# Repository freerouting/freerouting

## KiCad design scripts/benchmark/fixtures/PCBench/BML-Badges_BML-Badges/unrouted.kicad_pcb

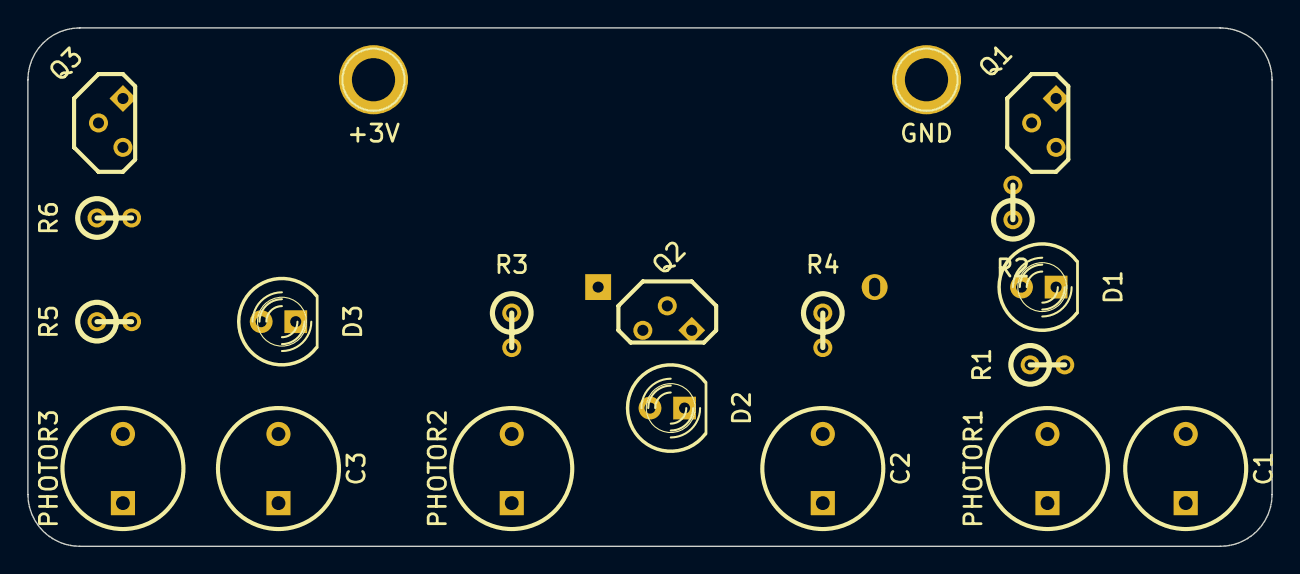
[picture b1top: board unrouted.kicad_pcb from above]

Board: 2 copper layers, 91.4 x 38.1 mm, 21 parts (1 on the bottom side), 11 nets, no tracks yet.

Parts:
BT1: 3V; BS-7-CR2032-2
C1, C2, C3: 22uF; C2V8
D1, D2, D3: LED; LED-5MM
P1: +3V; 1pin
P2: GND; 1pin
PHOTOR1, PHOTOR2, PHOTOR3: PHOTOR; LDR
Q1, Q2, Q3: PN2222A; TO92-EBC-num
R1, R3, R5: 330; R1
R2, R4, R6: 100k; R1

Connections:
3V: BT1.1, P1.1, R1.1, R2.1, R3.1, R4.1, R5.1, R6.1
GND: BT1.2, C1.2, C2.2, C3.2, P2.1, PHOTOR1.2, PHOTOR2.2, PHOTOR3.2, Q1.1, Q2.1, Q3.1
unnamed: C1.1, PHOTOR1.1, Q1.2, R2.2
unnamed: C2.1, PHOTOR2.1, Q2.2, R4.2
unnamed: C3.1, PHOTOR3.1, Q3.2, R6.2
unnamed: D1.1, R1.2
unnamed: D1.2, Q1.3
unnamed: D2.1, R3.2
unnamed: D2.2, Q2.3
unnamed: D3.1, R5.2
unnamed: D3.2, Q3.3

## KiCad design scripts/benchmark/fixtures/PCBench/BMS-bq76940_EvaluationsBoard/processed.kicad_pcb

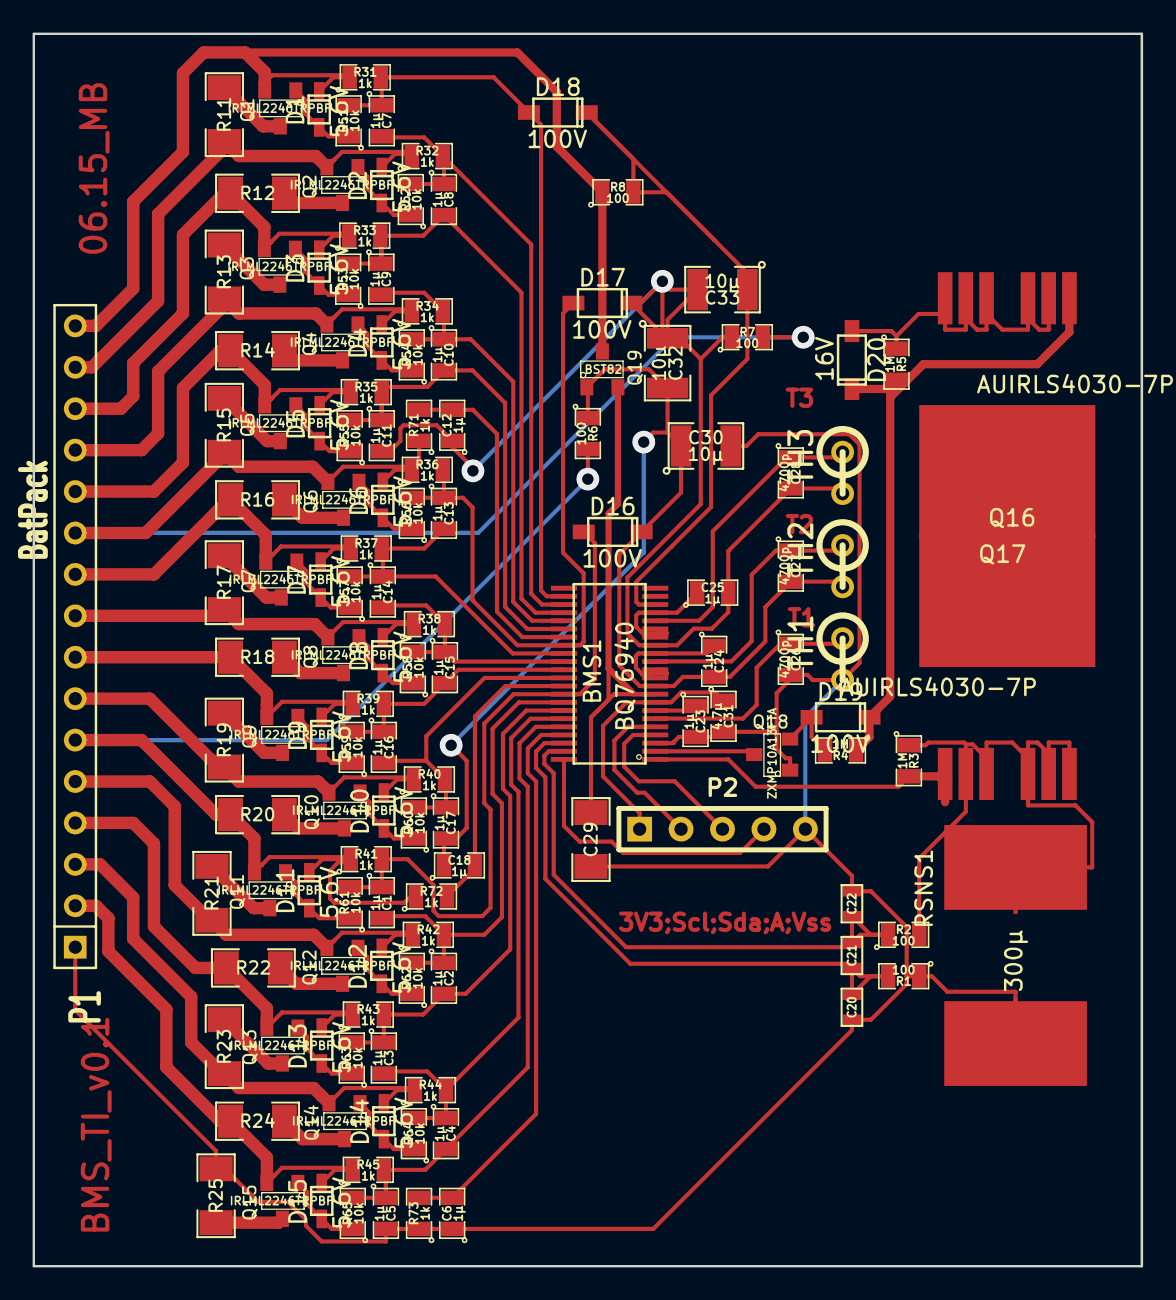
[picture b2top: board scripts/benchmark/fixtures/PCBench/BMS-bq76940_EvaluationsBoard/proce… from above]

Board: 2 copper layers, 67.9 x 75.6 mm, 134 parts (0 on the bottom side), 87 nets.

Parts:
BMS1: BQ76940
C1, C2, C3, C4, C5, C6, C7, C8, C9, C10, C11, C12, C13, C14, C15, C16, C17, C18, C23, C24, C25: 1µ; SM0805
C20, C21, C22: 0.1µ; SM0603
C26, C27, C28: 4700p; SM0805
C29: 1µ; SM1206
C30, C32, C33: 10µ; SM1210
C31: 4.7µ; SM0805
D1, D2, D3, D4, D5, D6, D7, D8, D9, D10, D11, D12, D13, D14, D15: 5.6V; SOD323
D16, D17, D18, D19: 100V; SOD123
D20: 16V; SOD123
P1: BatPack; SIL-16
P2: µC; PIN_ARRAY_5x1
Q1, Q2, Q3, Q4, Q5, Q6, Q7, Q8, Q9, Q10, Q11, Q12, Q13, Q14, Q15: IRLML2246TRPBF; SOT23
Q16, Q17: AUIRLS4030-7P
Q18: ZXMP10A13FTA; SOT23
Q19: BST82; SOT23
R1, R2, R6, R7, R8: 100; SM0805
R3, R4, R5: 1M; SM0805
R11, R12, R13, R14, R15, R16, R17, R18, R19, R20, R21, R22, R23, R24, R25: 39; SM1206
R31, R32, R33, R34, R35, R36, R37, R38, R39, R40, R41, R42, R43, R44, R45, R71, R72, R73: 1k; SM0805
R51, R52, R53, R54, R55, R56, R57, R58, R59, R60, R61, R62, R63, R64, R65: 10k; SM0805
RSNS1: 300µ; WSLP5931
TH1, TH2, TH3: THERMISTOR; R1

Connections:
/BatPack/C1: D15.2, P1.2, Q15.2, R24.1, R45.1
/BatPack/C2: D14.2, P1.3, Q14.2, R23.1, R44.1
/BatPack/C3: D13.2, P1.4, Q13.2, R22.1, R43.1
/BatPack/C4: D12.2, P1.5, Q12.2, R21.1, R42.1
/BatPack/C6: D10.2, P1.7, Q10.2, R19.1, R40.1
/BatPack/C7: D9.2, P1.8, Q9.2, R18.1, R39.1
/BatPack/C8: D8.2, P1.9, Q8.2, R17.1, R38.1
/BatPack/C9: D7.2, P1.10, Q7.2, R16.1, R37.1
/BatPack/C11: D5.2, P1.12, Q5.2, R14.1, R35.1
/BatPack/C12: D4.2, P1.13, Q4.2, R13.1, R34.1
/BatPack/C13: D3.2, P1.14, Q3.2, R12.1, R33.1
/BatPack/C14: D2.2, P1.15, Q2.2, R11.1, R32.1
/BatPack/VC0: BMS1.41, C6.2, R73.2
/BatPack/VC1: BMS1.40, C4.2, C5.1, R45.2, R65.2
/BatPack/VC2: BMS1.39, C3.2, C4.1, R44.2, R64.2
/BatPack/VC3: BMS1.38, C2.2, C3.1, R43.2, R63.2
/BatPack/VC4: BMS1.37, C1.2, C2.1, R42.2, R62.2
/BatPack/VC5: BMS1.36, C1.1, D16.1, R41.2, R61.2
/BatPack/VC6: BMS1.34, C16.2, C17.1, R40.2, R60.2
/BatPack/VC7: BMS1.33, C15.2, C16.1, R39.2, R59.2
/BatPack/VC8: BMS1.32, C14.2, C15.1, R38.2, R58.2
/BatPack/VC9: BMS1.31, C13.2, C14.1, R37.2, R57.2
/BatPack/VC10: BMS1.30, C13.1, D17.1, R36.2, R56.2
/BatPack/VC11: BMS1.28, C10.2, C11.1, R35.2, R55.2
/BatPack/VC12: BMS1.27, C9.2, C10.1, R34.2, R54.2
/BatPack/VC13: BMS1.26, C8.2, C9.1, R33.2, R53.2
/BatPack/VC14: BMS1.25, C7.2, C8.1, R32.2, R52.2
/BatPack/VC15: BMS1.24, C7.1, D18.1, R31.2, R51.2
/COM/BAT: BMS1.20, C33.1, D18.2, R8.2
/COM/CHG: BMS1.2, Q18.3
/COM/DSC: BMS1.1, Q16.1, R3.2
/COM/REGOUT: BMS1.8, C31.1, P2.1
/COM/REGSRC: BMS1.9, C29.1, Q19.2
/COM/SCL: BMS1.5, P2.2
/COM/SDA: BMS1.4, P2.3
/COM/SRN: BMS1.43, C21.2, C22.1, R2.1
/COM/SRP: BMS1.42, C20.2, C21.1, R1.2
A: D11.2, P1.6, Q11.2, R6.2, R20.1, R41.1, R72.1
ALERT: BMS1.44, P2.4
B: D6.2, P1.11, Q6.2, R7.2, R15.1, R36.1, R71.1
unnamed: D5.1, Q5.1, R55.1
unnamed: D3.1, Q3.1, R53.1
unnamed: D4.1, Q4.1, R54.1
unnamed: D6.1, Q6.1, R56.1
unnamed: D2.1, Q2.1, R52.1
unnamed: D1.1, Q1.1, R51.1
unnamed: Q3.3, R13.2
unnamed: Q4.3, R14.2
unnamed: Q5.3, R15.2
unnamed: Q6.3, R16.2
unnamed: Q7.3, R17.2
unnamed: Q8.3, R18.2
unnamed: D9.1, Q9.1, R59.1
unnamed: Q9.3, R19.2
unnamed: D10.1, Q10.1, R60.1
unnamed: Q1.3, R11.2
unnamed: Q2.3, R12.2
unnamed: Q14.3, R24.2
unnamed: Q13.3, R23.2
unnamed: Q12.3, R22.2
unnamed: Q11.3, R21.2
unnamed: Q10.3, R20.2
unnamed: Q15.3, R25.2
unnamed: D11.1, Q11.1, R61.1
unnamed: D12.1, Q12.1, R62.1
unnamed: D14.1, Q14.1, R64.1
unnamed: D7.1, Q7.1, R57.1
unnamed: D8.1, Q8.1, R58.1
unnamed: D13.1, Q13.1, R63.1
unnamed: D15.1, Q15.1, R65.1
unnamed: BMS1.7, C23.1
unnamed: BMS1.16, BMS1.17, BMS1.19, C25.1
unnamed: BMS1.11, BMS1.12, BMS1.14, C24.1
unnamed: D19.2, D20.2, Q17.1, R4.1, R5.2
unnamed: Q16.8, Q17.8
unnamed: D19.1, Q18.2, R4.2
unnamed: Q16.2, Q16.3, Q16.5, Q16.6, Q16.7, R2.2, R3.1, RSNS1.1
PACK+: D1.2, P1.16, Q1.2, Q19.3, R8.1, R31.1
PACK-: D20.1, Q17.2, Q17.3, Q17.5, Q17.6, Q17.7, R5.1
TS1: BMS1.6, C26.1, TH1.1
TS2: BMS1.13, C27.1, TH2.1
TS3: BMS1.18, C28.1, TH3.1
VC5B: BMS1.35, C18.2, R72.2
VC5x: BMS1.10, C17.2, C18.1, C24.2, C27.2, C30.1, C32.2, D16.2, Q19.1, R6.1, TH2.2
VC10B: BMS1.29, C12.2, R71.2
VC10x: BMS1.15, C11.2, C12.1, C25.2, C28.2, C32.1, C33.2, D17.2, R7.1, TH3.2
VSS: BMS1.3, C5.2, C6.1, C20.1, C22.2, C23.2, C26.2, C29.2, C30.2, C31.2, P1.1, P2.5, Q18.1, R1.1, R25.1, R73.1, RSNS1.2, TH1.2

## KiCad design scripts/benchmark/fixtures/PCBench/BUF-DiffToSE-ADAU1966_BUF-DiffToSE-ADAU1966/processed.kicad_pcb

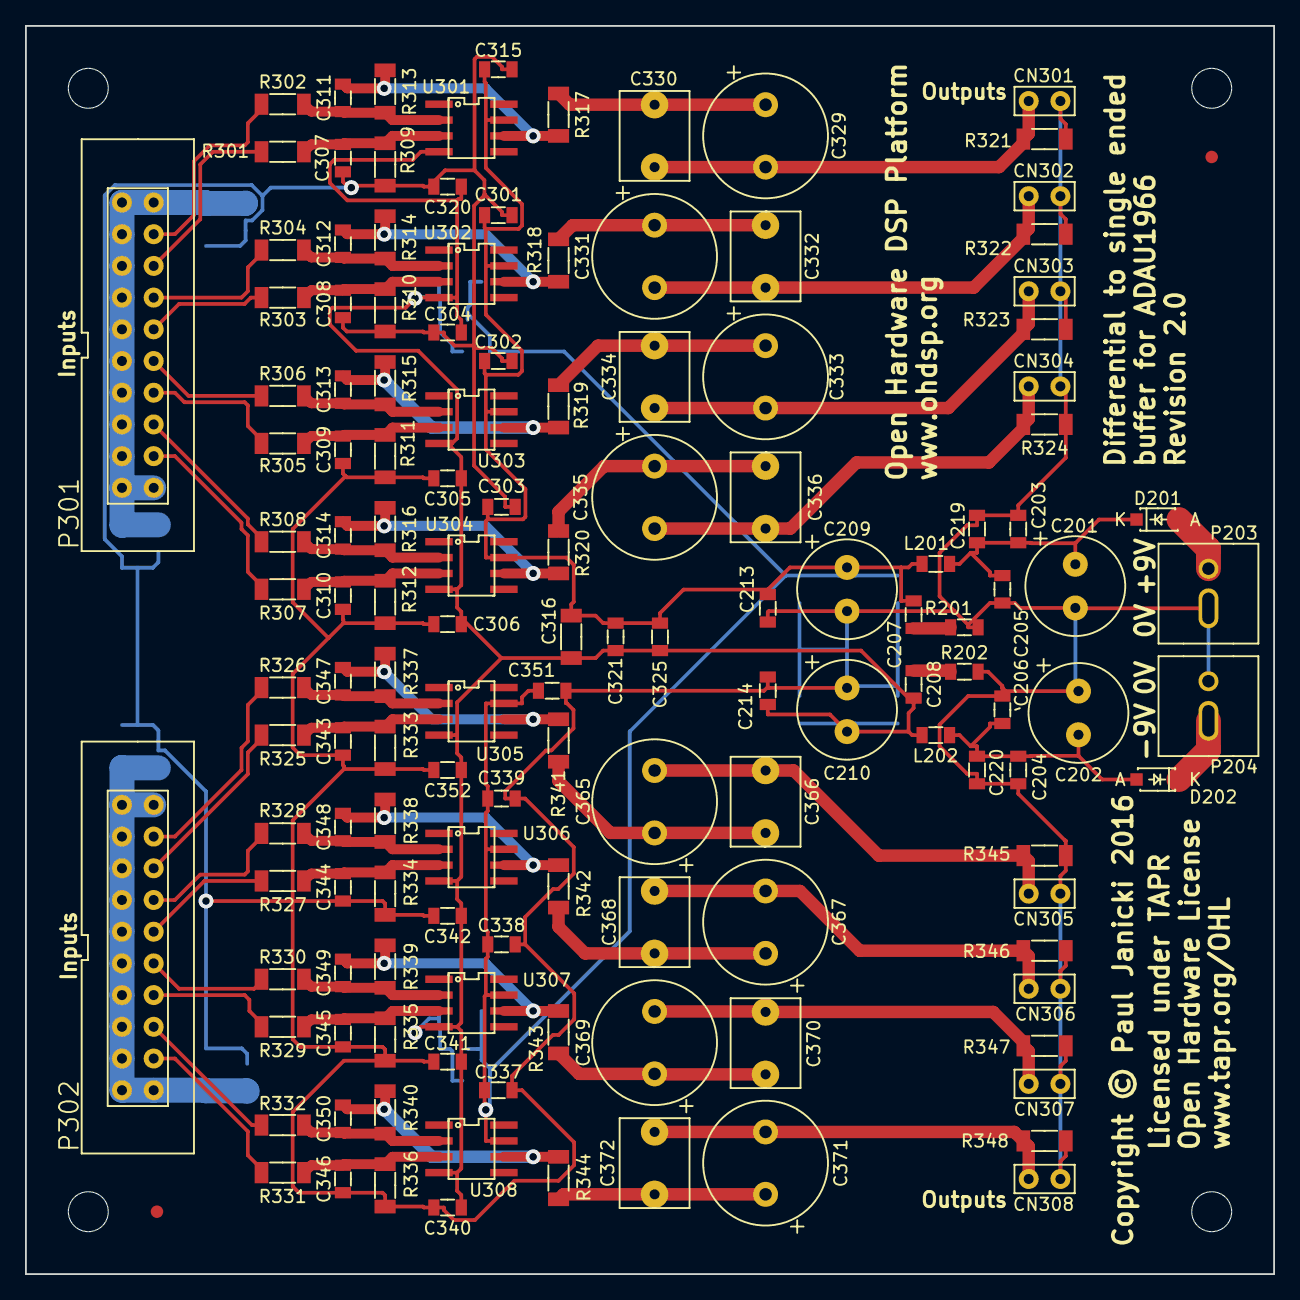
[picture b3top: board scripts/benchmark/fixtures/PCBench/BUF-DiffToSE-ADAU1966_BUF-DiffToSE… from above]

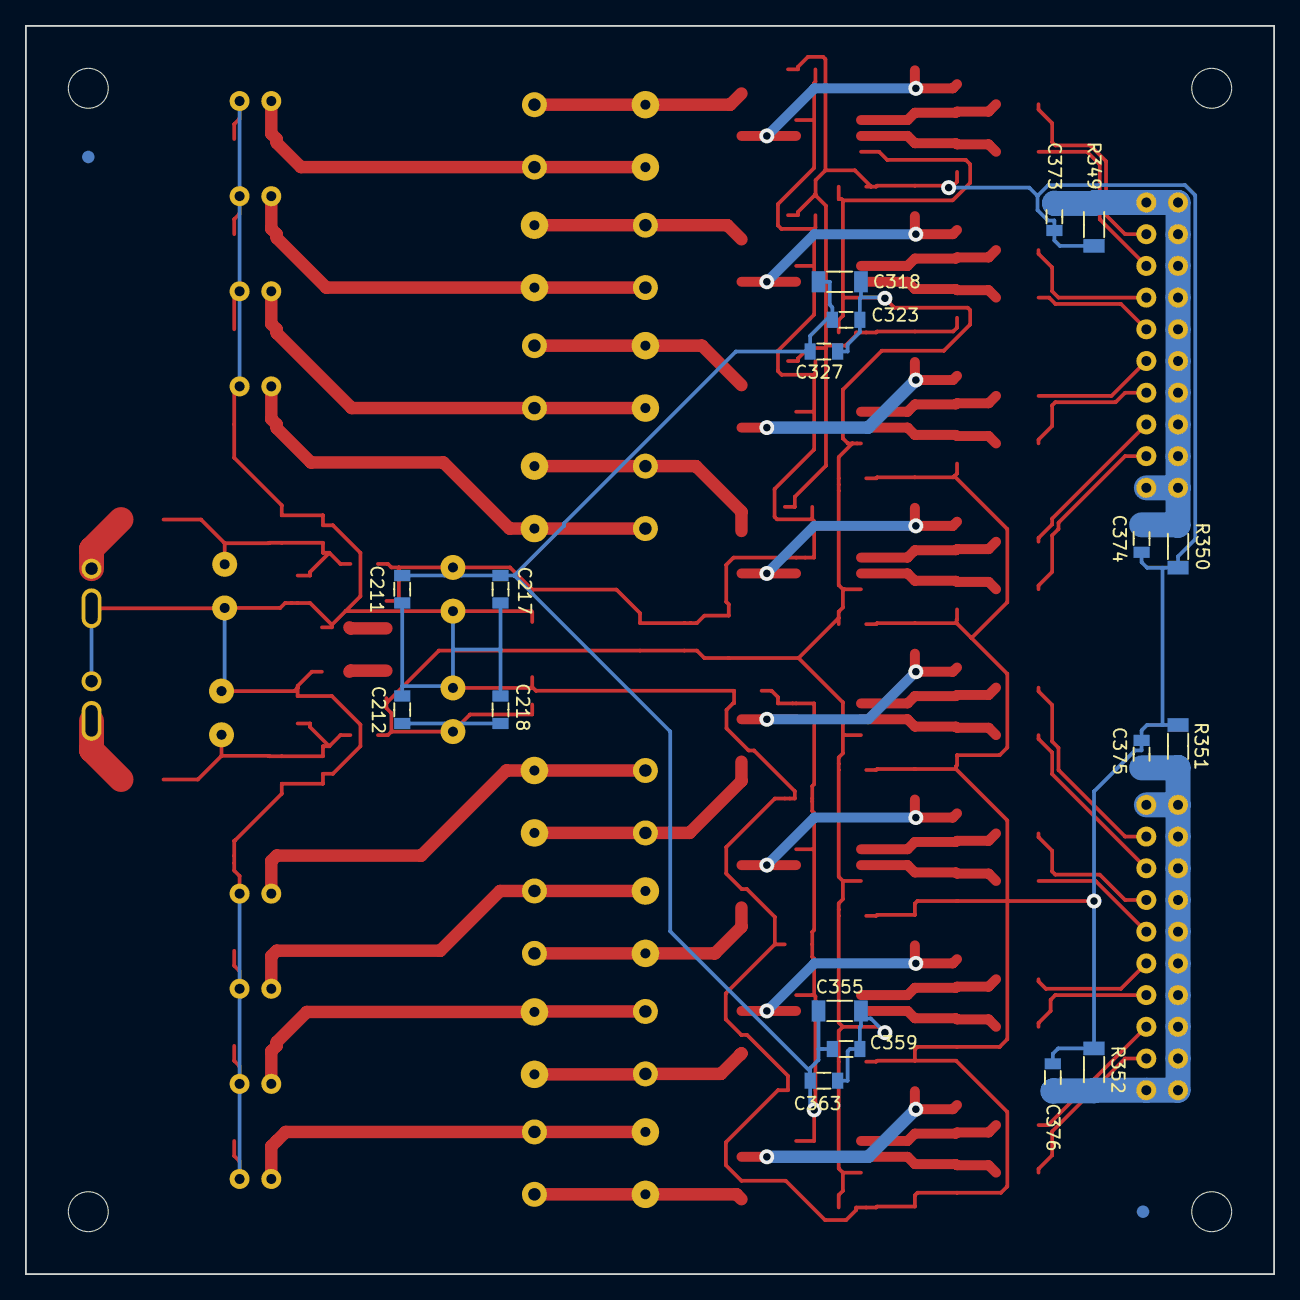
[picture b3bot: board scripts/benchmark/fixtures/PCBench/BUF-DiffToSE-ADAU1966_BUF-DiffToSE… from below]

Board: 2 copper layers, 100.0 x 100.0 mm, 165 parts (20 on the bottom side), 67 nets.

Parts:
C201, C202, C209, C210: 220u; CAP-TH-D8mmP3.5mm
C203, C204, C211, C212, C301, C302, C303, C304, C305, C306, C315, C320, C321, C323, C337, C338, C339, C340, C341, C342, C351, C352, C359, C373, C374, C375, C376: 100n; SMD-0805
C205, C206, C213, C214, C325, C327, C363: 10n; SMD-0805
C207, C208: 100p; SMD-0805
C217, C218, C219, C220: 22u; SMD-0805
C307, C308, C309, C310, C311, C312, C313, C314, C343, C344, C345, C346, C347, C348, C349, C350: 1n; SMD-0805
C316, C318, C355: 10u; SMD-1206
C329, C331, C333, C335, C365, C367, C369, C371: 100u; CAP-TH-D10mmP5mm
C330, C332, C334, C336, C366, C368, C370, C372: 100n; CAP_TH_5mm
CN301, CN302, CN303, CN304, CN305, CN306, CN307, CN308: COAX; CONN_SIL_2
D201, D202: SS14L; DIODE-SOD-123
FID1, FID2, FID3, FID4: MNT_HOLE; FID-1MM-3MM
L201, L202: 600R@100MHz; SMD-0805
MNT201, MNT202, MNT203, MNT204: MNT_HOLE; MNT_HOLE_3.2mm
P203, P204: CONN_2x1; CONN-2WAY-2.54mm-3.81mm-SPACING
P301, P302: CONN_02X10; CONN_DIL_2X10_BOX
R201, R202: 47; SMD-0805
R301, R302, R303, R304, R305, R306, R307, R308, R325, R326, R327, R328, R329, R330, R331, R332: 1k3; SMD-1206
R309, R310, R311, R312, R313, R314, R315, R316, R333, R334, R335, R336, R337, R338, R339, R340: 1k5; SMD-1206
R317, R318, R319, R320, R341, R342, R343, R344: 100; SMD-1206
R321, R322, R323, R324, R345, R346, R347, R348: 100k; SMD-1206
R349, R350, R351, R352: 10; SMD-1206
U301, U302, U303, U304, U305, U306, U307, U308: TLE2071; IC_SOIC_8

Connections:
+9VA: C207.1, C209.1, C211.1, C213.1, C217.1, C301.1, C302.1, C303.1, C315.1, C316.1, C318.1, C321.1, C323.1, C325.1, C327.1, C337.1, C338.1, C339.1, C351.1, C355.1, C359.1, C363.1, L201.2, U301.7, U302.7, U303.7, U304.7, U305.7, U306.7, U307.7, U308.7
-9VA: C208.2, C210.2, C212.2, C214.2, C218.2, C304.2, C305.2, C306.2, C316.2, C318.2, C320.2, C321.2, C323.2, C325.2, C327.2, C340.2, C341.2, C342.2, C352.2, C355.2, C359.2, C363.2, L202.2, U301.4, U302.4, U303.4, U304.4, U305.4, U306.4, U307.4, U308.4
GNDA: C201.2, C202.1, C203.2, C204.1, C205.2, C206.1, C209.2, C210.1, C211.2, C212.1, C213.2, C214.1, C217.2, C218.1, C219.2, C220.1, C301.2, C302.2, C303.2, C304.1, C305.1, C306.1, C307.2, C308.2, C309.2, C310.2, C315.2, C320.1, C337.2, C338.2, C339.2, C340.1, C341.1, C342.1, C343.2, C344.2, C345.2, C346.2, C351.2, C352.1, C373.2, C374.2, C375.2, C376.2, CN301.2, CN302.2, CN303.2, CN304.2, CN305.2, CN306.2, CN307.2, CN308.2, P203.2, P204.1, R201.2, R202.1, R309.1, R310.1, R311.1, R312.1, R321.1, R322.1, R323.1, R324.1, R333.1, R334.1, R335.1, R336.1, R345.1, R346.1, R347.1, R348.1, R349.1, R350.1, R351.1, R352.1
unnamed: C201.1, C203.1, C205.1, C219.1, D201.2, L201.1
unnamed: C202.2, C204.2, C206.2, C220.2, D202.1, L202.1
unnamed: C207.2, R201.1
unnamed: C208.1, R202.2
unnamed: C307.1, R301.1, R309.2, U301.3
unnamed: C308.1, R303.1, R310.2, U302.3
unnamed: C309.1, R305.1, R311.2, U303.3
unnamed: C310.1, R307.1, R312.2, U304.3
unnamed: C311.1, R302.1, R313.2, U301.2
unnamed: C311.2, R313.1, R317.2, U301.6
unnamed: C312.1, R304.1, R314.2, U302.2
unnamed: C312.2, R314.1, R318.2, U302.6
unnamed: C313.1, R306.1, R315.2, U303.2
unnamed: C313.2, R315.1, R319.2, U303.6
unnamed: C314.1, R308.1, R316.2, U304.2
unnamed: C314.2, R316.1, R320.2, U304.6
unnamed: C329.1, C330.1, R317.1
unnamed: C329.2, C330.2, CN301.1, R321.2
unnamed: C331.1, C332.1, R318.1
unnamed: C331.2, C332.2, CN302.1, R322.2
unnamed: C333.1, C334.1, R319.1
unnamed: C333.2, C334.2, CN303.1, R323.2
unnamed: C335.1, C336.1, R320.1
unnamed: C335.2, C336.2, CN304.1, R324.2
unnamed: C343.1, R325.1, R333.2, U305.3
unnamed: C344.1, R327.1, R334.2, U306.3
unnamed: C345.1, R329.1, R335.2, U307.3
unnamed: C346.1, R331.1, R336.2, U308.3
unnamed: C347.1, R326.1, R337.2, U305.2
unnamed: C347.2, R337.1, R341.2, U305.6
unnamed: C348.1, R328.1, R338.2, U306.2
unnamed: C348.2, R338.1, R342.2, U306.6
unnamed: C349.1, R330.1, R339.2, U307.2
unnamed: C349.2, R339.1, R343.2, U307.6
unnamed: C350.1, R332.1, R340.2, U308.2
unnamed: C350.2, R340.1, R344.2, U308.6
unnamed: C365.1, C366.1, R341.1
unnamed: C365.2, C366.2, CN305.1, R345.2
unnamed: C367.1, C368.1, R342.1
unnamed: C367.2, C368.2, CN306.1, R346.2
unnamed: C369.1, C370.1, R343.1
unnamed: C369.2, C370.2, CN307.1, R347.2
unnamed: C371.1, C372.1, R344.1
unnamed: C371.2, C372.2, CN308.1, R348.2
unnamed: C373.1, C374.1, P301.1, P301.2, P301.3, P301.5, P301.7, P301.9, P301.11, P301.13, P301.15, P301.17, P301.19, P301.20, R349.2, R350.2
unnamed: C375.1, C376.1, P302.1, P302.2, P302.3, P302.5, P302.7, P302.9, P302.11, P302.13, P302.15, P302.17, P302.19, P302.20, R351.2, R352.2
unnamed: D201.1, P203.1
unnamed: D202.2, P204.2
unnamed: P301.4, R302.2
unnamed: P301.6, R301.2
unnamed: P301.8, R304.2
unnamed: P301.10, R303.2
unnamed: P301.12, R306.2
unnamed: P301.14, R305.2
unnamed: P301.16, R308.2
unnamed: P301.18, R307.2
unnamed: P302.4, R326.2
unnamed: P302.6, R325.2
unnamed: P302.8, R328.2
unnamed: P302.10, R327.2
unnamed: P302.12, R330.2
unnamed: P302.14, R329.2
unnamed: P302.16, R332.2
unnamed: P302.18, R331.2

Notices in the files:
scripts/benchmark/fixtures/PCBench/BUF-DiffToSE-ADAU1966_BUF-DiffToSE-ADAU1966/processed.kicad_pcb:
Licensed under the TAPR Open Hardware License (www.tapr.org/OHL). This documentation
Copyright Paul Janicki 2016
Copyright © Paul Janicki 2016
Licensed under TAPR
